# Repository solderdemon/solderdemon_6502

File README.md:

# SolderDemon 6502

## Overview

SolderDemon 6502 is a programmable, extensible 8-bit retro computer built around the WDC 65C02,
and the mainboard of SolderDemon's 6502 line. This repository holds its design files, firmware
and software.

It is based on [rosco_6502](https://github.com/rosco-m68k/rosco_6502) (CERN OHL). r1 is rosco_6502 r4
with its glue logic moved into one ATF1502AS CPLD; it was developed here as "r5", and the
[revision notes](docs/revision-5.md) still use that name.

Revision r1 — a 100 × 100 mm board. J5 stands beside the CPU; CPU, bank RAM, low RAM and ROM run side by side under the top edge, the CPLD and DUART sockets sit on one line below them with the SolderDemon logo and JTAG between, and the indicators, RESET and all resistors form the bottom row. Their references are on the component side. The UART and SD/SPI connectors are straight pin headers along the right edge. J5 is a right-angle socket on the left edge, so the host stands upright in the busboard's HOST slot; the standalone CS2 pin header is removed ([layout and mounting notes](docs/layout-r1.md)).

## Start here

- [KiCad project](design/solderdemon_6502.kicad_pro)
- [Schematic (PDF)](manufacturing/solderdemon_6502-schematic.pdf)
- [Getting started](docs/getting-started.md)
- [Gerbers and drill files](manufacturing/solderdemon_6502-r1-gerbers.zip)

### Documentation

Start with the [documentation index](docs/README.md).

* [Getting started and terminal setup](docs/getting-started.md)
* [Hardware and memory map](docs/hardware.md)
* [Building and programming ROM](docs/rom-firmware.md)
* [Building and programming PLDs](docs/pld-firmware.md)
* [Developing and loading programs](docs/software.md)
* [Troubleshooting](docs/troubleshooting.md)
* [Revision 4 notes](docs/revision-4.md)
* [SolderDemon 6502 r1 notes](docs/revision-5.md) (developed as r5)
* [SolderDemon 6502 r1 layout](docs/layout-r1.md)

## Board views

| Top Side | Bottom Side |
|:---:|:---:|
|  |  |

## Hardware

### Specifications

The hardware specifications for the SolderDemon 6502 are:

* WDC 65C02 at up-to 14MHz (In theory, 10MHz testing target currently).
* SCN68681C1A44 provides two UARTs, timers and SD Card / SPI / GPIO; the console runs at 38400 bit/s
* 528KB RAM
  * 16KB low RAM ($0000 - $3FFF)
  * 16 x 32KB RAM banks ($4000 - $BFFF)
* 8KB IO space ($C000 - $DFFF)
* 8KB or 32KB (banked) ROM $E000 - $FFFF
* High-speed decode and glue logic handled by Atmel F22V10C PLDs (r4), or by a single ATF1502AS CPLD programmed in the board over JTAG (SolderDemon r1, see [r1 notes](docs/revision-5.md)).
* Comprehensive expansion and IO connectors allow the system to be easily expanded!

You can see the electrical designs in [kicad](design). Programmable logic lives in [pld](code/firmware/pld).

### Design history

The r4 import and the initial CPLD design are retained as generator inputs. See the upstream rosco_6502 repository for the original development history.

## Using the board

### Software

The current firmware uses the cc65 toolchain (`ca65`, `ld65` and `da65`).
It includes hardware initialization, WozMon, SD card access, read-only FAT32
support and boot code that looks for `/ROSC0DE_6502.BIN` on the SD card.
The firmware and filesystem utilities are still under development.

See the [firmware README](code/firmware/README.md) for build
instructions.

### Related tools

* [rosco CLI](https://github.com/solderdemon/rosco-cli): a cross-platform `rosco` command
  that creates, builds and uploads rosco_6502 (and rosco_m68k) programs over UART, or
  runs them in the emulator.
* [rosco-emulator](https://github.com/solderdemon/rosco-emulator): a slimmed-down MAME
  build that emulates the rosco_6502 r4, so programs and firmware can be tested without
  the board.

See [Developing and loading programs](docs/software.md#rosco-cli-and-emulator) for usage.

## Build and verification

### Verification

See the [layout checks](docs/layout-r1.md) and [CPLD build and programming guide](docs/pld-firmware.md). The [fabrication files](manufacturing/) include the schematic, Gerbers and drill files.

<!-- repository-layout -->
## Repository layout

- [`design/`](design/solderdemon_6502.kicad_pro) holds the KiCad project, schematic, PCB and local libraries.
- [`code/firmware/`](code/firmware/) — ROM and programmable-logic sources and programming files.
- [`code/software/`](code/software/) — Example programs and filesystem utilities.
- [`code/build/`](code/build/) — Local build products.
- [`tools/`](tools/) — Design generators and verification.
- [`manufacturing/`](manufacturing/) — Fabrication files and schematic PDF.
- [`images/`](images/) — Board views and artwork.

Open the project in `design/`. Use the scripts in `tools/` to change the design. The `.kicad_pro` file holds the DRC rules.
The r1 placement scripts are in `tools/`. To rebuild the reviewed 5.08 mm capacitor
placement from `design/placement_before_5mm_caps.kicad_pcb.gz`, run
`tools/upgrade_100nf.py`, then `tools/route_r5.py` to redraw the signal tracks.
<!-- /repository-layout -->

## Licences and attribution

- **Hardware:** [CERN Open Hardware Licence v1.2](LICENCE.hardware.txt).
- **Software:** [MIT](LICENSE).
- **Documentation:** [Creative Commons Attribution 2.0 UK](https://creativecommons.org/licenses/by/2.0/uk/).

Based on [rosco_6502](https://github.com/rosco-m68k/rosco_6502) r4, © 2022–2023 Ross Bamford & Contributors. SolderDemon changes include the CPLD glue logic, r1 board layout and build documentation. Copyright © 2026 SolderDemon. Original authorship and licence notices are retained.

The USB-Blaster patch applies to the OpenOCD 0.12.0 driver under the GNU GPL.
See [the GPL text](licenses/GPL-2.0.txt) and [OpenOCD](https://github.com/openocd-org/openocd/tree/v0.12.0).

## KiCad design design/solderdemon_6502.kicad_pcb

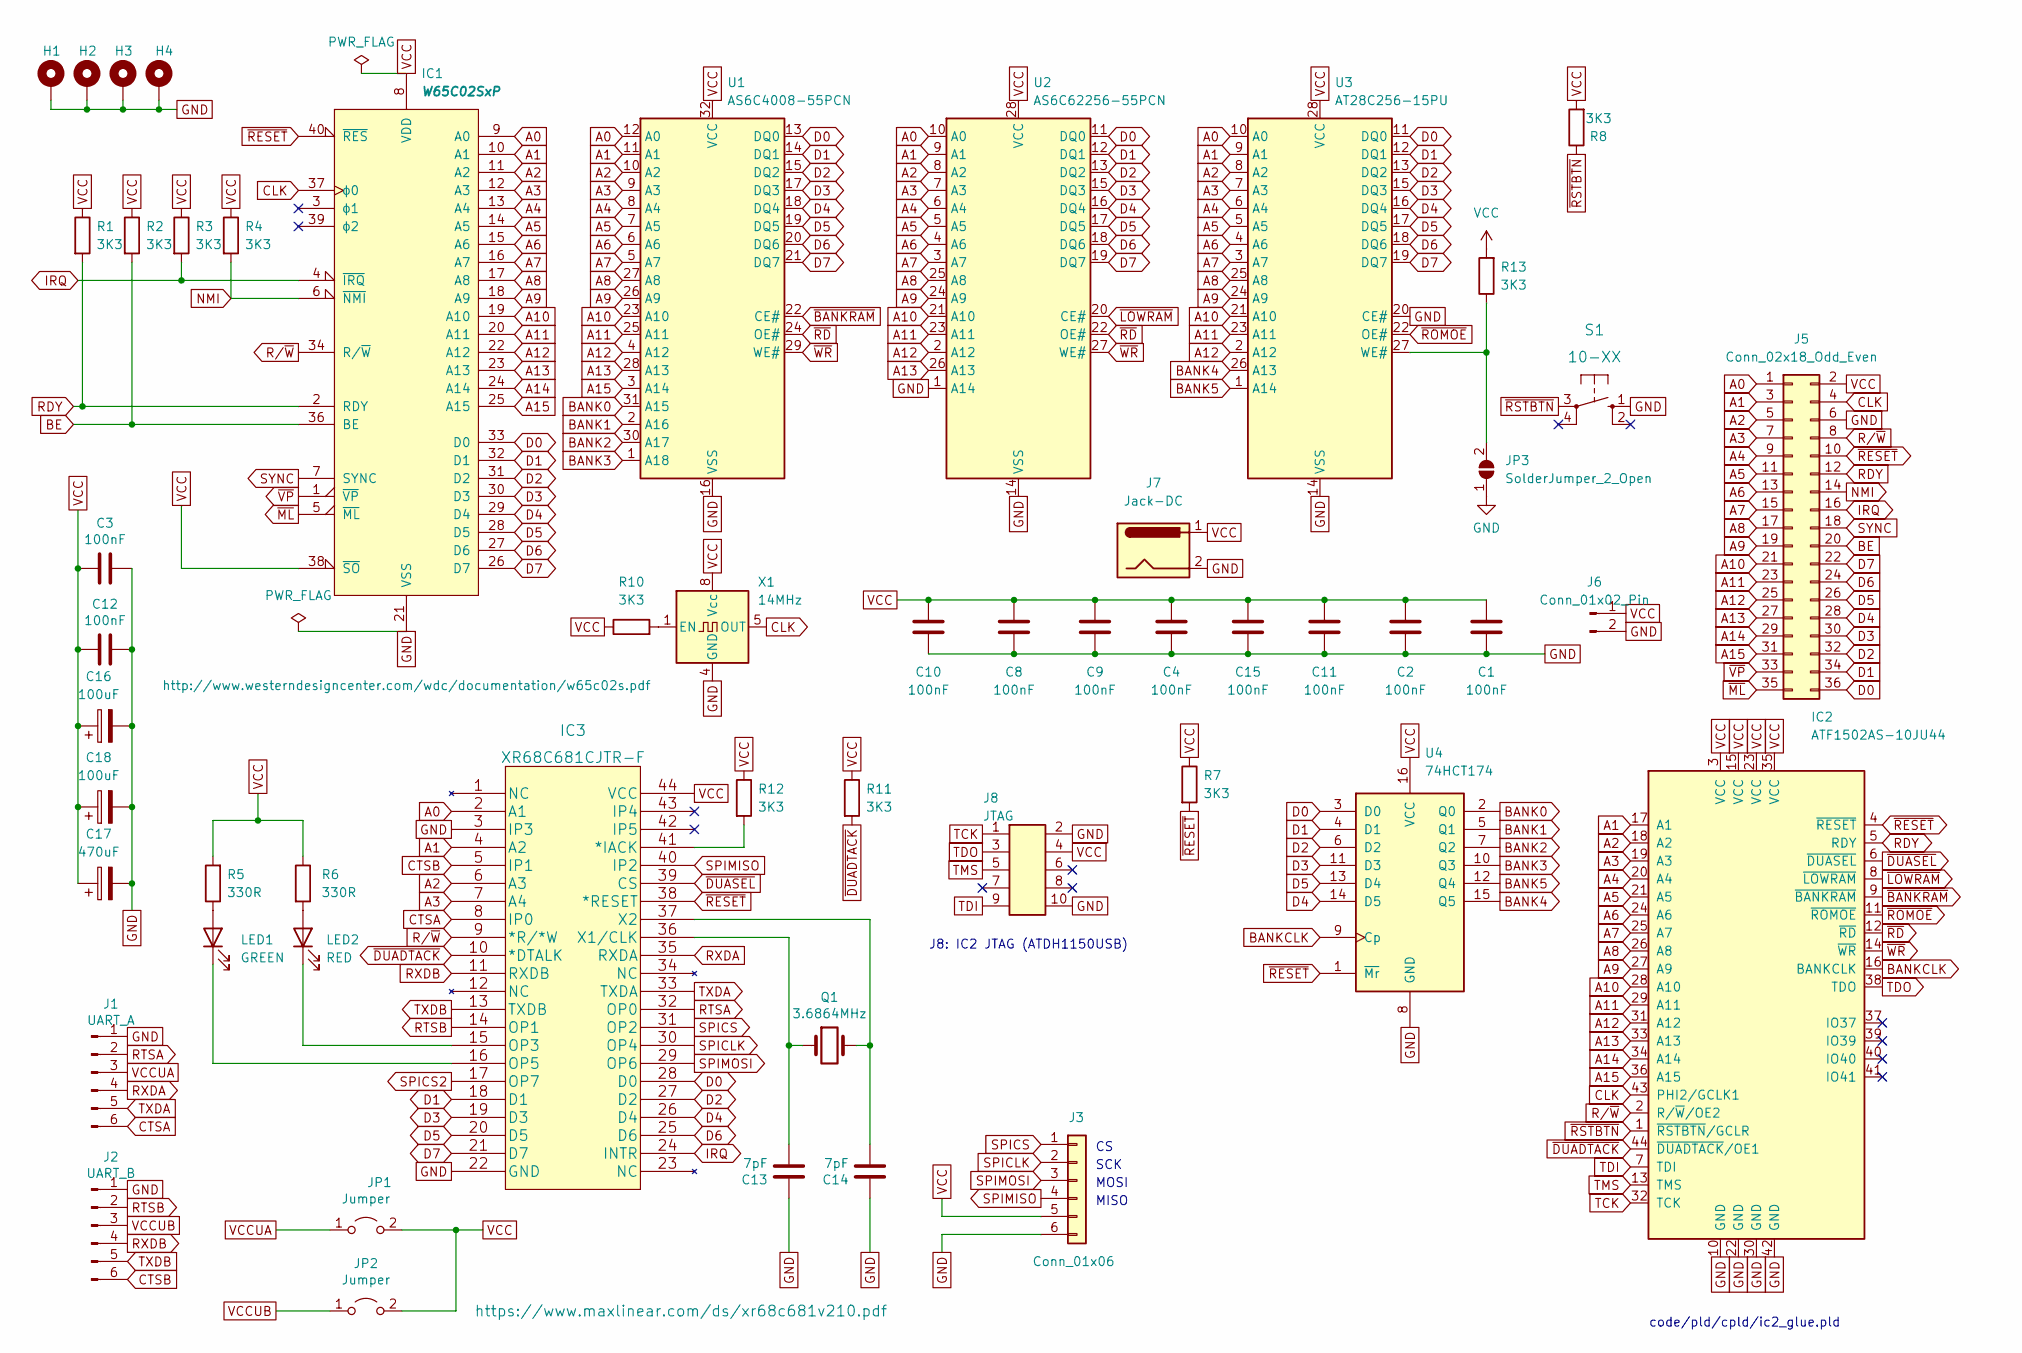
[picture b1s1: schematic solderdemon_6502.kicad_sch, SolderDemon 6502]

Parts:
C1, C2, C3, C4, C8, C9, C10, C11, C12, C15: 100nF; C_Radial_5.08mm
C13, C14: 7pF; C2.5_or_3.5-3
C16, C18: 100uF; CP_Radial_D6.3mm_P2.50mm
C17: 470uF; CP_Radial_D7.5mm_P2.50mm
H1, H2, H3, H4: MountingHole_Pad; MountingHole_3.5mm_Pad
IC1: W65C02SxP; DIP-40_W15.24mm_Socket_LongPads
IC2: ATF1502AS-10JU44; PLCC-44_THT-Socket
IC3: XR68C681CJTR-F; PLCC-44_THT-Socket
J1: UART_A; PinHeader_1x06_P2.54mm_Vertical
J2: UART_B; PinHeader_1x06_P2.54mm_Vertical
J3: Conn_01x06; PinHeader_1x06_P2.54mm_Vertical
J5: Conn_02x18_Odd_Even; PinSocket_2x18_P2.54mm_Horizontal_EdgeMount
J6: Conn_01x02_Pin; PinHeader_1x02_P2.54mm_Vertical
J7: Jack-DC; BarrelJack_Horizontal
J8: JTAG; PinHeader_2x05_P2.54mm_Vertical
JP1, JP2: Jumper; PinHeader_1x02_P2.54mm_Vertical
JP3: SolderJumper_2_Open; SolderJumper-2_P1.3mm_Open_TrianglePad1.0x1.5mm
LED1: GREEN; LED_D5.0mm
LED2: RED; LED_D5.0mm
Q1: 3.6864MHz; Crystal_HC49-4H_Vertical
R1, R2, R3, R4, R7, R8, R10, R11, R12, R13: 3K3; R_Axial_DIN0207_L6.3mm_D2.5mm_P10.16mm_Horizontal
R5, R6: 330R; R_Axial_DIN0207_L6.3mm_D2.5mm_P10.16mm_Horizontal
S1: 10-XX; B3F-10XX
U1: AS6C4008-55PCN; DIP-32_W15.24mm_Socket_LongPads
U2: AS6C62256-55PCN; DIP-28_W15.24mm_Socket_LongPads
U3: AT28C256-15PU; DIP-28_W15.24mm_Socket_LongPads
U4: 74HCT174; DIP-16_W7.62mm_Socket_LongPads
X1: 14MHz; Oscillator_DIP-8

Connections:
A0: IC1.9 (A0), IC3.2 (A1), J5.1, U1.12 (A0), U2.10 (A0), U3.10 (A0)
A1: IC1.10 (A1), IC2.17 (OP7), IC3.4 (A2), J5.3, U1.11 (A1), U2.9 (A1), U3.9 (A1)
A2: IC1.11 (A2), IC2.18 (D1), IC3.6 (A3), J5.5, U1.10 (A2), U2.8 (A2), U3.8 (A2)
A3: IC1.12 (A3), IC2.19 (D3), IC3.7 (A4), J5.7, U1.9 (A3), U2.7 (A3), U3.7 (A3)
A4: IC1.13 (A4), IC2.20 (D5), J5.9, U1.8 (A4), U2.6 (A4), U3.6 (A4)
A5: IC1.14 (A5), IC2.21 (D7), J5.11, U1.7 (A5), U2.5 (A5), U3.5 (A5)
A6: IC1.15 (A6), IC2.24 (INTR), J5.13, U1.6 (A6), U2.4 (A6), U3.4 (A6)
A7: IC1.16 (A7), IC2.25 (D6), J5.15, U1.5 (A7), U2.3 (A7), U3.3 (A7)
A8: IC1.17 (A8), IC2.26 (D4), J5.17, U1.27 (A8), U2.25 (A8), U3.25 (A8)
A9: IC1.18 (A9), IC2.27 (D2), J5.19, U1.26 (A9), U2.24 (A9), U3.24 (A9)
A10: IC1.19 (A10), IC2.28 (D0), J5.21, U1.23 (A10), U2.21 (A10), U3.21 (A10)
A11: IC1.20 (A11), IC2.29 (OP6), J5.23, U1.25 (A11), U2.23 (A11), U3.23 (A11)
A12: IC1.22 (A12), IC2.31 (OP2), J5.25, U1.4 (A12), U2.2 (A12), U3.2 (A12)
A13: IC1.23 (A13), IC2.33 (TXDA), J5.27, U1.28 (A13), U2.26 (A13)
A14: IC1.24 (A14), IC2.34 (NC), J5.29
A15: IC1.25 (A15), IC2.36 (X1/CLK), J5.31, U1.3 (A14)
BANK0: U1.31 (A15), U4.2 (Q0)
BANK1: U1.2 (A16), U4.5 (Q1)
BANK2: U1.30 (A17), U4.7 (Q2)
BANK3: U1.1 (A18), U4.10 (Q3)
BANK4: U3.26 (A13), U4.15 (Q5)
BANK5: U3.1 (A14), U4.12 (Q4)
BANKCLK: IC2.16 (OP5), U4.9 (Cp)
BE: IC1.36 (BE), J5.20, R2.2
CLK: IC1.37 (ϕ0), IC2.43 (IP4), J5.4, X1.5 (OUT)
CTSA: IC3.8 (IP0), J1.6
CTSB: IC3.5 (IP1), J2.6
D0: IC1.33 (D0), IC3.28 (D0), J5.36, U1.13 (DQ0), U2.11 (DQ0), U3.11 (DQ0), U4.3 (D0)
D1: IC1.32 (D1), IC3.18 (D1), J5.34, U1.14 (DQ1), U2.12 (DQ1), U3.12 (DQ1), U4.4 (D1)
D2: IC1.31 (D2), IC3.27 (D2), J5.32, U1.15 (DQ2), U2.13 (DQ2), U3.13 (DQ2), U4.6 (D2)
D3: IC1.30 (D3), IC3.19 (D3), J5.30, U1.17 (DQ3), U2.15 (DQ3), U3.15 (DQ3), U4.11 (D3)
D4: IC1.29 (D4), IC3.26 (D4), J5.28, U1.18 (DQ4), U2.16 (DQ4), U3.16 (DQ4), U4.14 (D5)
D5: IC1.28 (D5), IC3.20 (D5), J5.26, U1.19 (DQ5), U2.17 (DQ5), U3.17 (DQ5), U4.13 (D4)
D6: IC1.27 (D6), IC3.25 (D6), J5.24, U1.20 (DQ6), U2.18 (DQ6), U3.18 (DQ6)
D7: IC1.26 (D7), IC3.21 (D7), J5.22, U1.21 (DQ7), U2.19 (DQ7), U3.19 (DQ7)
GND: C1.1, C2.1, C3.1, C4.1, C8.1, C9.1, C10.1, C11.1, C12.1, C13.1, C14.1, C15.1, C16.2, C17.2, C18.2, H1.1, H2.1, H3.1, H4.1, IC1.21 (VSS), IC2.10 (*DTALK), IC2.22 (GND), IC2.30 (OP4), IC2.42 (IP5), IC3.3 (IP3), IC3.22 (GND), J1.1, J2.1, J3.6, J5.6, J6.2, J7.2, J8.2, J8.10, JP3.1 (A), S1.1 (S), U1.16 (VSS), U2.1 (A14), U2.14 (VSS), U3.14 (VSS), U3.20 (CE#), U4.8 (GND), X1.4 (GND)
IRQ: IC1.4 (~IRQ), IC3.24 (INTR), J5.16, R3.2
NMI: IC1.6 (~NMI), J5.14, R4.2
unnamed: IC3.41 (*IACK), R12.2
unnamed: IC3.15 (OP3), LED2.1 (K)
unnamed: IC3.16 (OP5), LED1.1 (K)
unnamed: C13.2, IC3.36 (X1/CLK), Q1.1
unnamed: C14.2, IC3.37 (X2), Q1.2
unnamed: JP3.2 (B), R13.1, U3.27 (WE#)
unnamed: LED1.2 (A), R5.1
unnamed: LED2.2 (A), R6.2
unnamed: R10.2, X1.1 (EN)
RDY: IC1.2 (RDY), IC2.5 (IP1), J5.12, R1.2
RTSA: IC3.32 (OP0), J1.2
RTSB: IC3.14 (OP1), J2.2
RXDA: IC3.35 (RXDA), J1.4
RXDB: IC3.11 (RXDB), J2.4
SPICLK: IC3.30 (OP4), J3.2
SPICS: IC3.31 (OP2), J3.1
SPICS2: IC3.17 (OP7)
SPIMISO: IC3.40 (IP2), J3.4
SPIMOSI: IC3.29 (OP6), J3.3
SYNC: IC1.7 (SYNC), J5.18
TCK: IC2.32 (OP0), J8.1
TDI: IC2.7 (A4), J8.9
TDO: IC2.38 (*RESET), J8.3
TMS: IC2.13 (TXDB), J8.5
TXDA: IC3.33 (TXDA), J1.5
TXDB: IC3.13 (TXDB), J2.5
VCC: C1.2, C2.2, C3.2, C4.2, C8.2, C9.2, C10.2, C11.2, C12.2, C15.2, C16.1, C17.1, C18.1, IC1.8 (VDD), IC1.38 (~SO), IC2.3 (IP3), IC2.15 (OP3), IC2.23 (NC), IC2.35 (RXDA), IC3.44 (VCC), J3.5, J5.2, J6.1, J7.1, J8.4, JP1.2 (B), JP2.2 (B), R1.1, R2.1, R3.1, R4.1, R5.2, R6.1, R7.1, R8.2, R10.1, R11.1, R12.1, R13.2, U1.32 (VCC), U2.28 (VCC), U3.28 (VCC), U4.16 (VCC), X1.8 (Vcc)
VCCUA: J1.3, JP1.1 (A)
VCCUB: J2.3, JP2.1 (A)
~BANKRAM: IC2.9 (*R/*W), U1.22 (CE#)
~DUADTACK: IC2.44 (VCC), IC3.10 (*DTALK), R11.2
~DUASEL: IC2.6 (A3), IC3.39 (CS)
~LOWRAM: IC2.8 (IP0), U2.20 (CE#)
~ML: IC1.5 (~ML), J5.35
~RD: IC2.12 (NC), U1.24 (OE#), U2.22 (OE#)
~RESET: IC1.40 (~RES), IC2.4 (A2), IC3.38 (*RESET), J5.10, R7.2, U4.1 (~Mr)
~ROMOE: IC2.11 (RXDB), U3.22 (OE#)
~RSTBTN: IC2.1 (NC), R8.1, S1.3
~VP: IC1.1 (~VP), J5.33
~WR: IC2.14 (OP1), U1.29 (WE#), U2.27 (WE#)

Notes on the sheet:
SCK
MOSI
MISO
code/pld/cpld/ic2_glue.pld
J8: IC2 JTAG (ATDH1150USB)

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
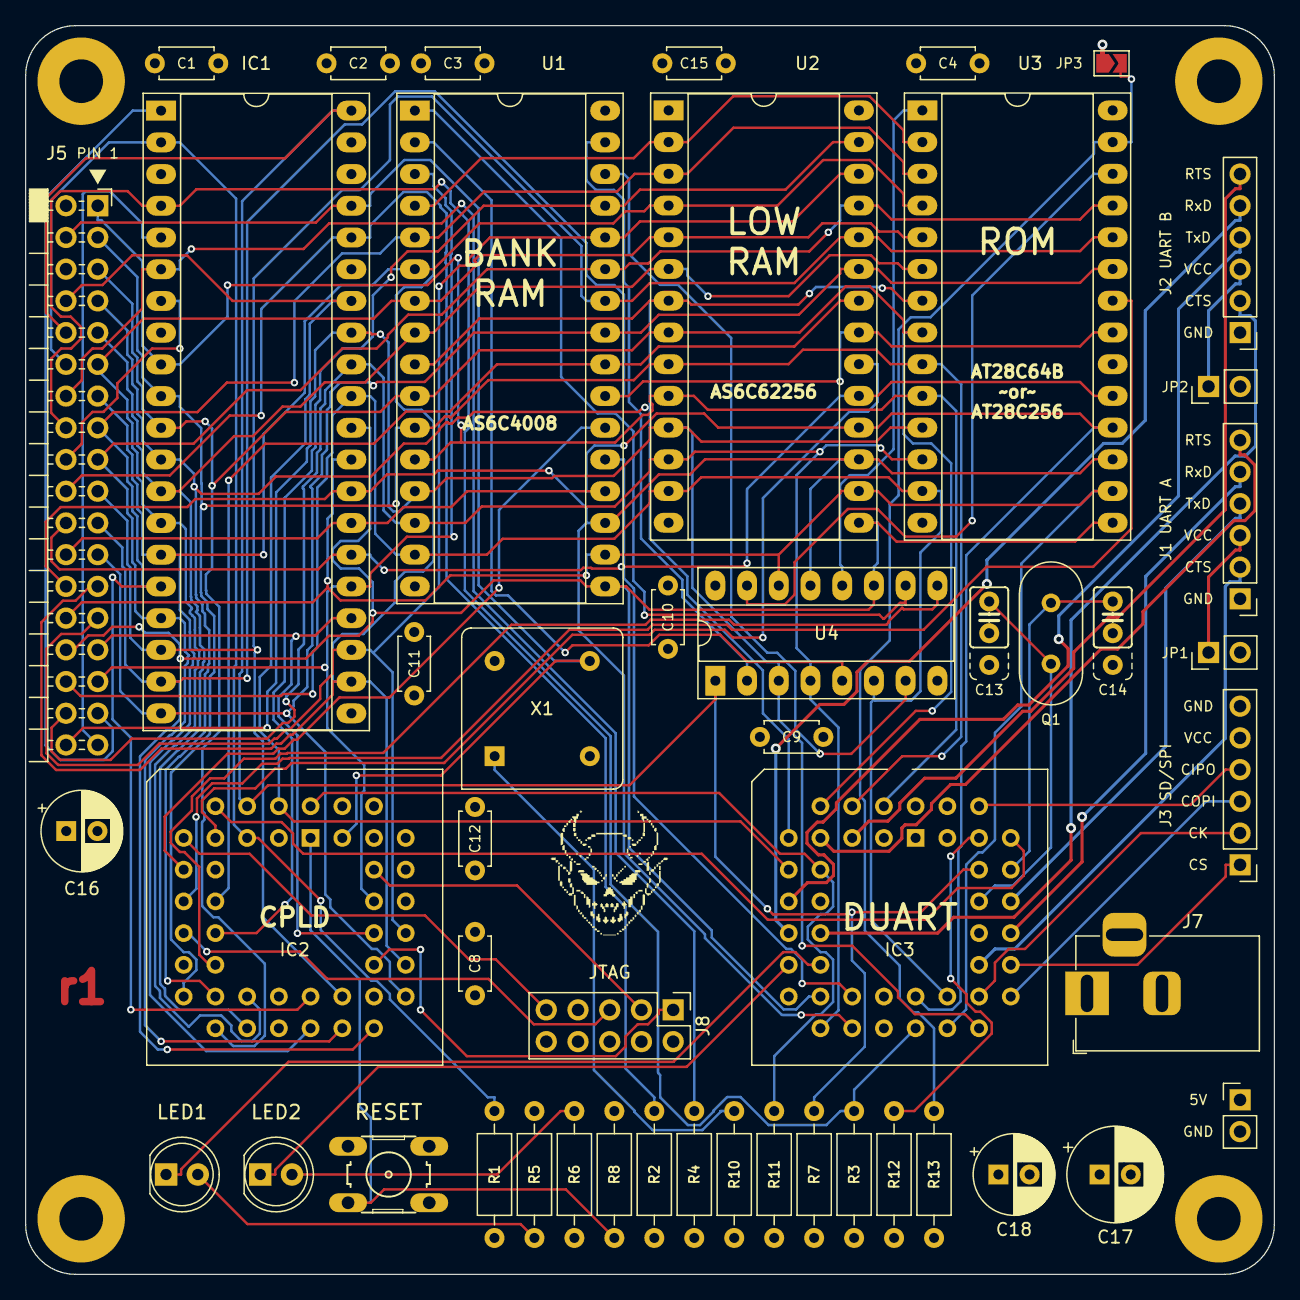
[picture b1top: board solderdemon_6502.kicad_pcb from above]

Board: 4 copper layers, 100.0 x 100.0 mm, 54 parts (0 on the bottom side), 78 nets.

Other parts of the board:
LOGO1: SolderDemon_Logo

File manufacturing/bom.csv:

Designator,Footprint,Quantity,Value,LCSC Part #
"C1, C10, C11, C12, C15, C2, C3, C4, C8, C9",C_Radial_5.08mm,10,100nF,
"C13, C14",C2.5_or_3.5-3,2,7pF,
"C16, C18",CP_Radial_D6.3mm_P2.50mm,2,100uF,
C17,CP_Radial_D7.5mm_P2.50mm,1,470uF,
"H1, H2, H3, H4",MountingHole_3.5mm_Pad,4,MountingHole_Pad,
IC1,DIP-40_W15.24mm_Socket_LongPads,1,W65C02SxP,
IC2,PLCC-44_THT-Socket,1,ATF1502AS-10JU44,
IC3,PLCC-44_THT-Socket,1,XR68C681CJTR-F,
J1,PinHeader_1x06_P2.54mm_Vertical,1,UART_A,
J2,PinHeader_1x06_P2.54mm_Vertical,1,UART_B,
J3,PinHeader_1x06_P2.54mm_Vertical,1,Conn_01x06,
J5,PinSocket_2x18_P2.54mm_Horizontal_EdgeMount,1,Conn_02x18_Odd_Even,
J6,PinHeader_1x02_P2.54mm_Vertical,1,Conn_01x02_Pin,
J7,BarrelJack_Horizontal,1,Jack-DC,
J8,PinHeader_2x05_P2.54mm_Vertical,1,JTAG,
"JP1, JP2",PinHeader_1x02_P2.54mm_Vertical,2,Jumper,
JP3,SolderJumper-2_P1.3mm_Open_TrianglePad1.0x1.5mm,1,SolderJumper_2_Open,
LED1,LED_D5.0mm,1,GREEN,
LED2,LED_D5.0mm,1,RED,
Q1,Crystal_HC49-4H_Vertical,1,3.6864MHz,
"R1, R10, R11, R12, R13, R2, R3, R4, R7, R8",R_Axial_DIN0207_L6.3mm_D2.5mm_P10.16mm_Horizontal,10,3K3,
"R5, R6",R_Axial_DIN0207_L6.3mm_D2.5mm_P10.16mm_Horizontal,2,330R,
S1,B3F-10XX,1,10-XX,
U1,DIP-32_W15.24mm_Socket_LongPads,1,AS6C4008-55PCN,
U2,DIP-28_W15.24mm_Socket_LongPads,1,AS6C62256-55PCN,
U3,DIP-28_W15.24mm_Socket_LongPads,1,AT28C256-15PU,
U4,DIP-16_W7.62mm_Socket_LongPads,1,74HCT174,
X1,Oscillator_DIP-8,1,14MHz,

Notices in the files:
design/kicad/solderdemon_6502.kicad_sch:
Copyright (c)2026 SolderDemon
Open Source Hardware (CERN OHL v1.2)
Modified 2026-09-30 from rosco_6502 r4, (c)2022-2023 Ross Bamford & Contributors
